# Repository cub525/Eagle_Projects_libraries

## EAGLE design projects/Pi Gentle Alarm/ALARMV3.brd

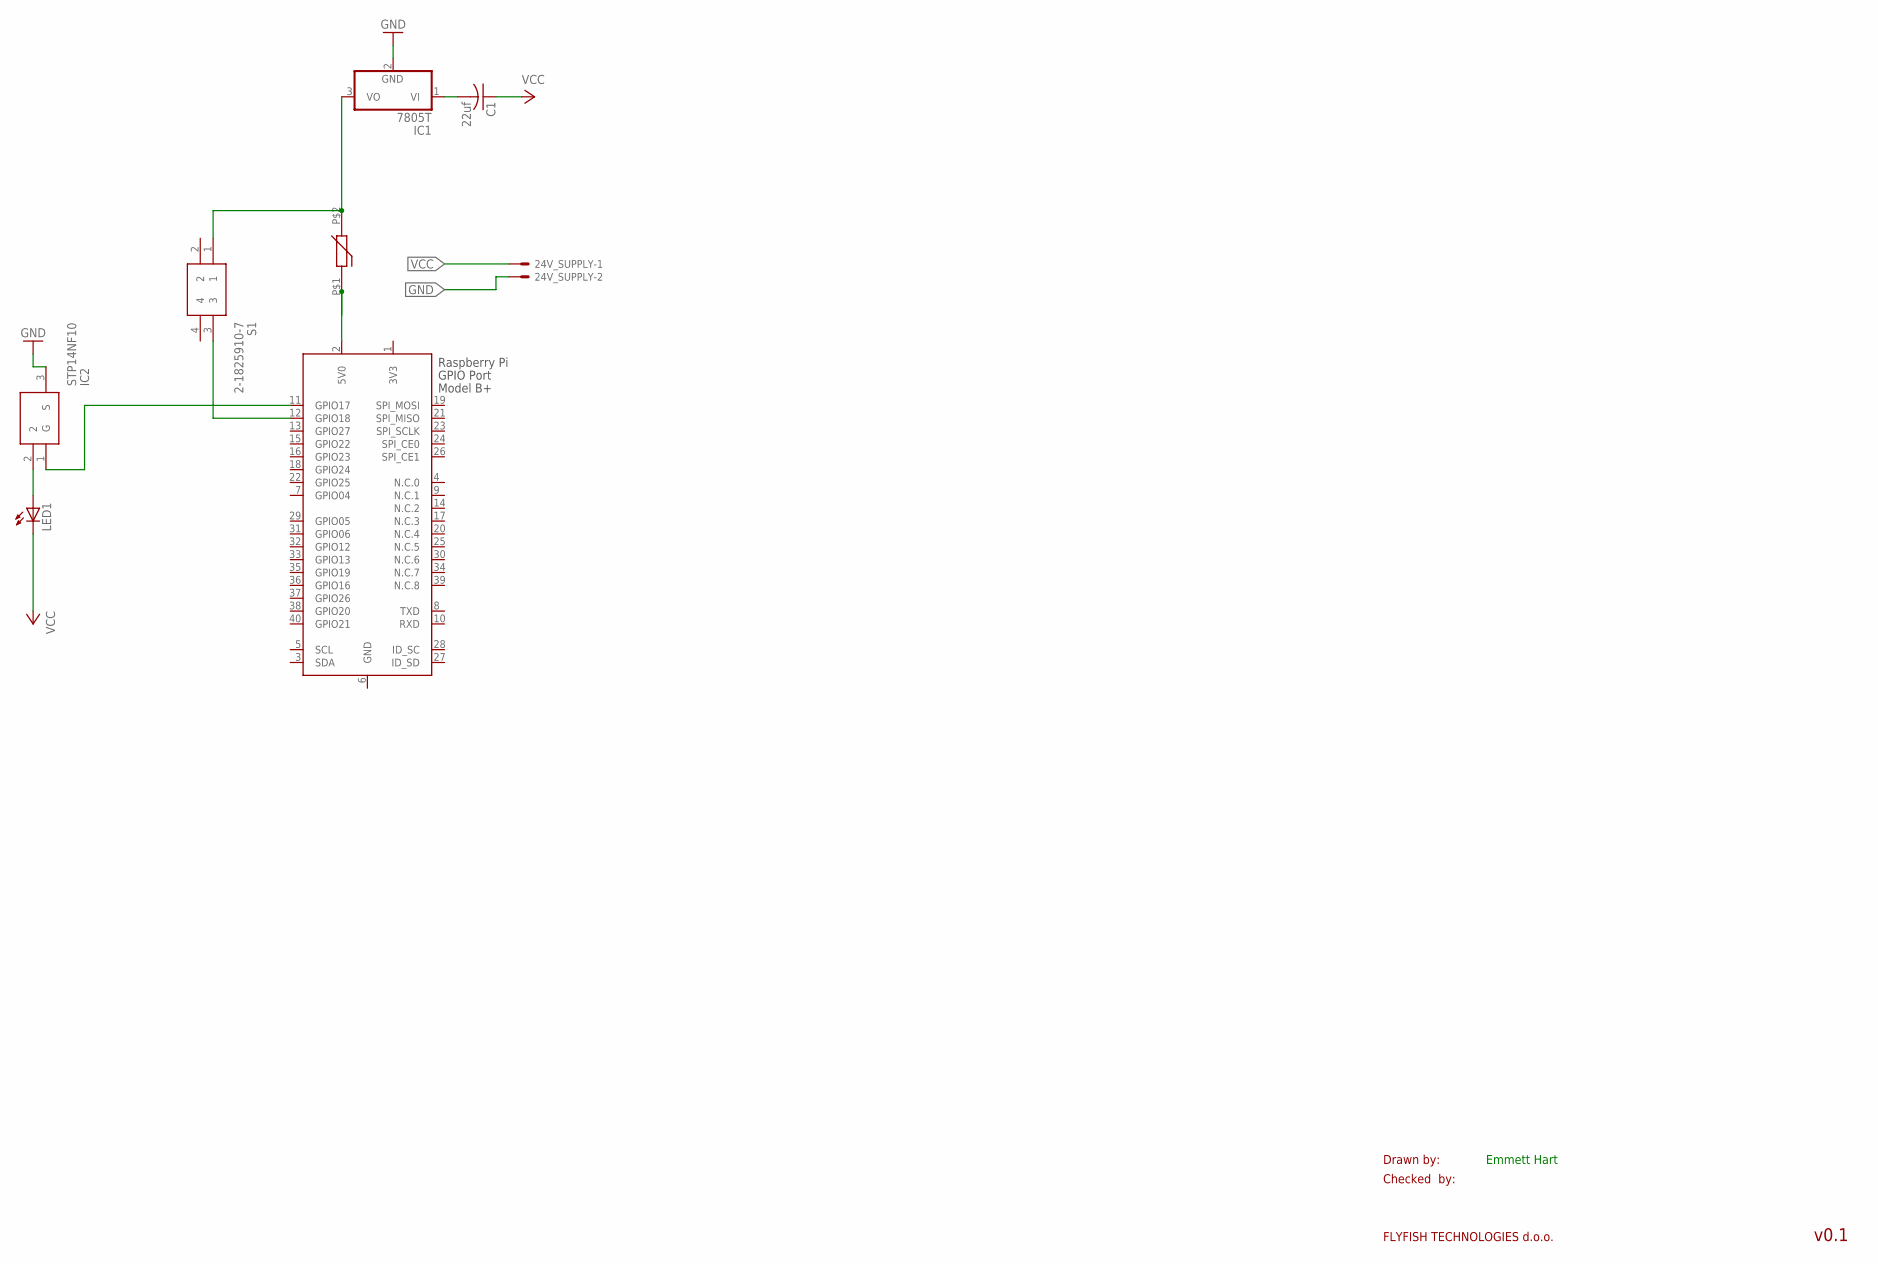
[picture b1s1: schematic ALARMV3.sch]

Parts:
24V_SUPPLY: 22-23-2021
C1: 22uf; C050-024X044
F1: MF-MSMF260-2
IC1: 7805T; TO220H; MPN NCP7805TG
IC2: STP14NF10; TO270P460X1020X2008-3P
LED1: LEDSFH482; SFH482
S1: 2-1825910-7; TE-6MM-TACT-SWITCH
X1: RASPI_BOARD_B+_E0; RASPI_BOARD_B+_EDGES_0DRILL

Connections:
3V3: X1.1 (3V3)
GND: 24V_SUPPLY.2, IC1.2 (GND), IC2.3 (S), X1.6 (GND)
GPIO17: IC2.1 (G), X1.11 (GPIO17)
unnamed: F1.P$1, X1.2 (5V0)
unnamed: S1.3, X1.12 (GPIO18)
unnamed: C1.2, IC1.1 (VI)
unnamed: F1.P$2, IC1.3 (VO), S1.1
unnamed: IC2.2, LED1.A
VCC: 24V_SUPPLY.1, C1.1, LED1.K (C)

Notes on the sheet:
Drawn by:
Checked by:
FLYFISH TECHNOLOGIES d.o.o.
v0.1
Emmett Hart

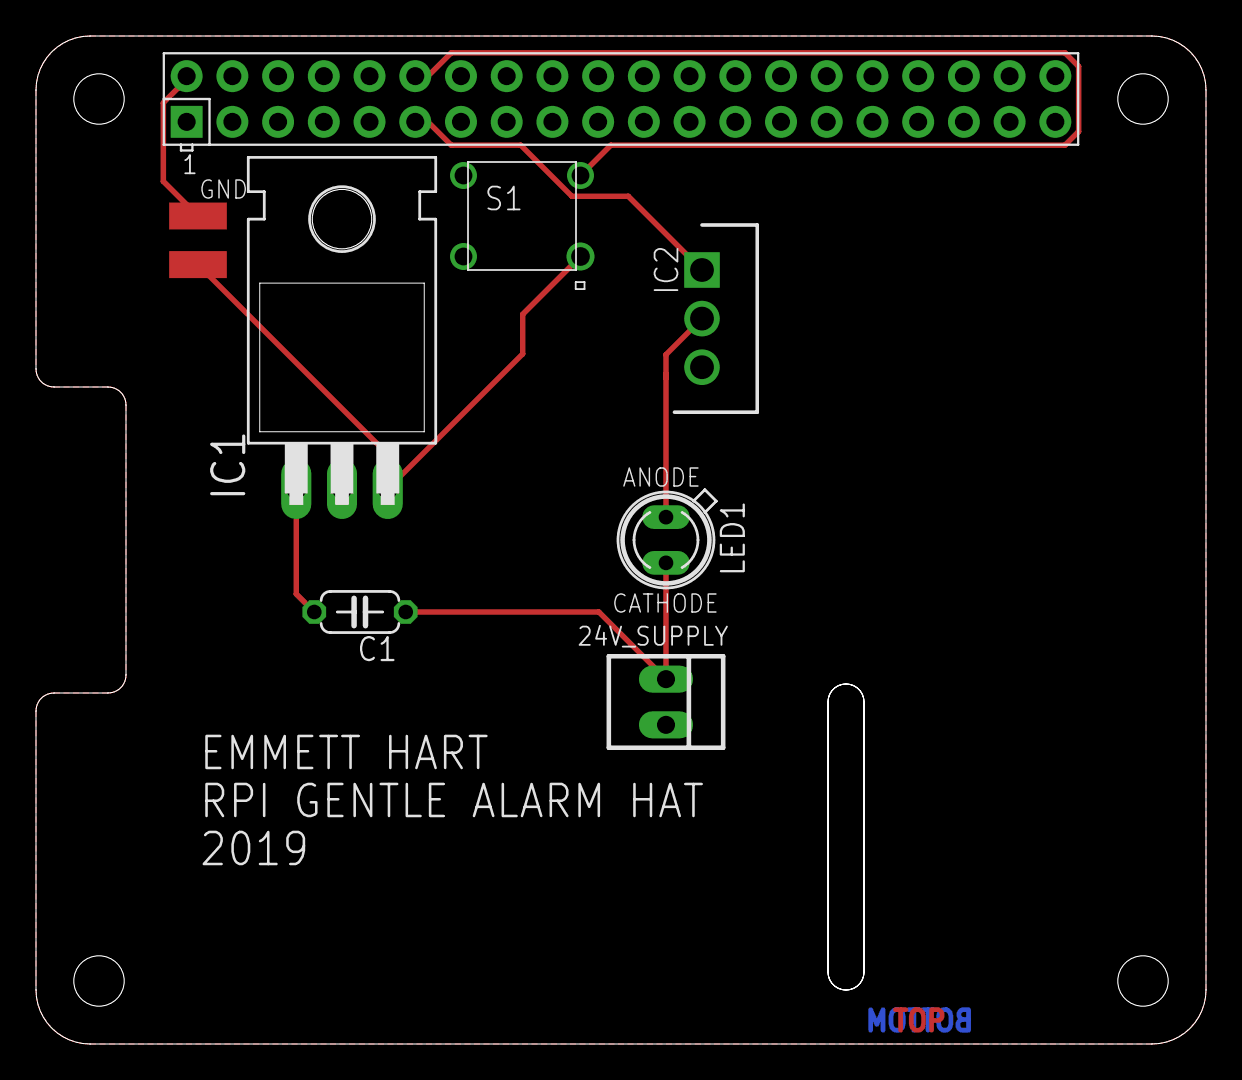
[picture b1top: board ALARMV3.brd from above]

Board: 2 copper layers, 65.0 x 56.0 mm, 8 parts (0 on the bottom side), 8 nets.

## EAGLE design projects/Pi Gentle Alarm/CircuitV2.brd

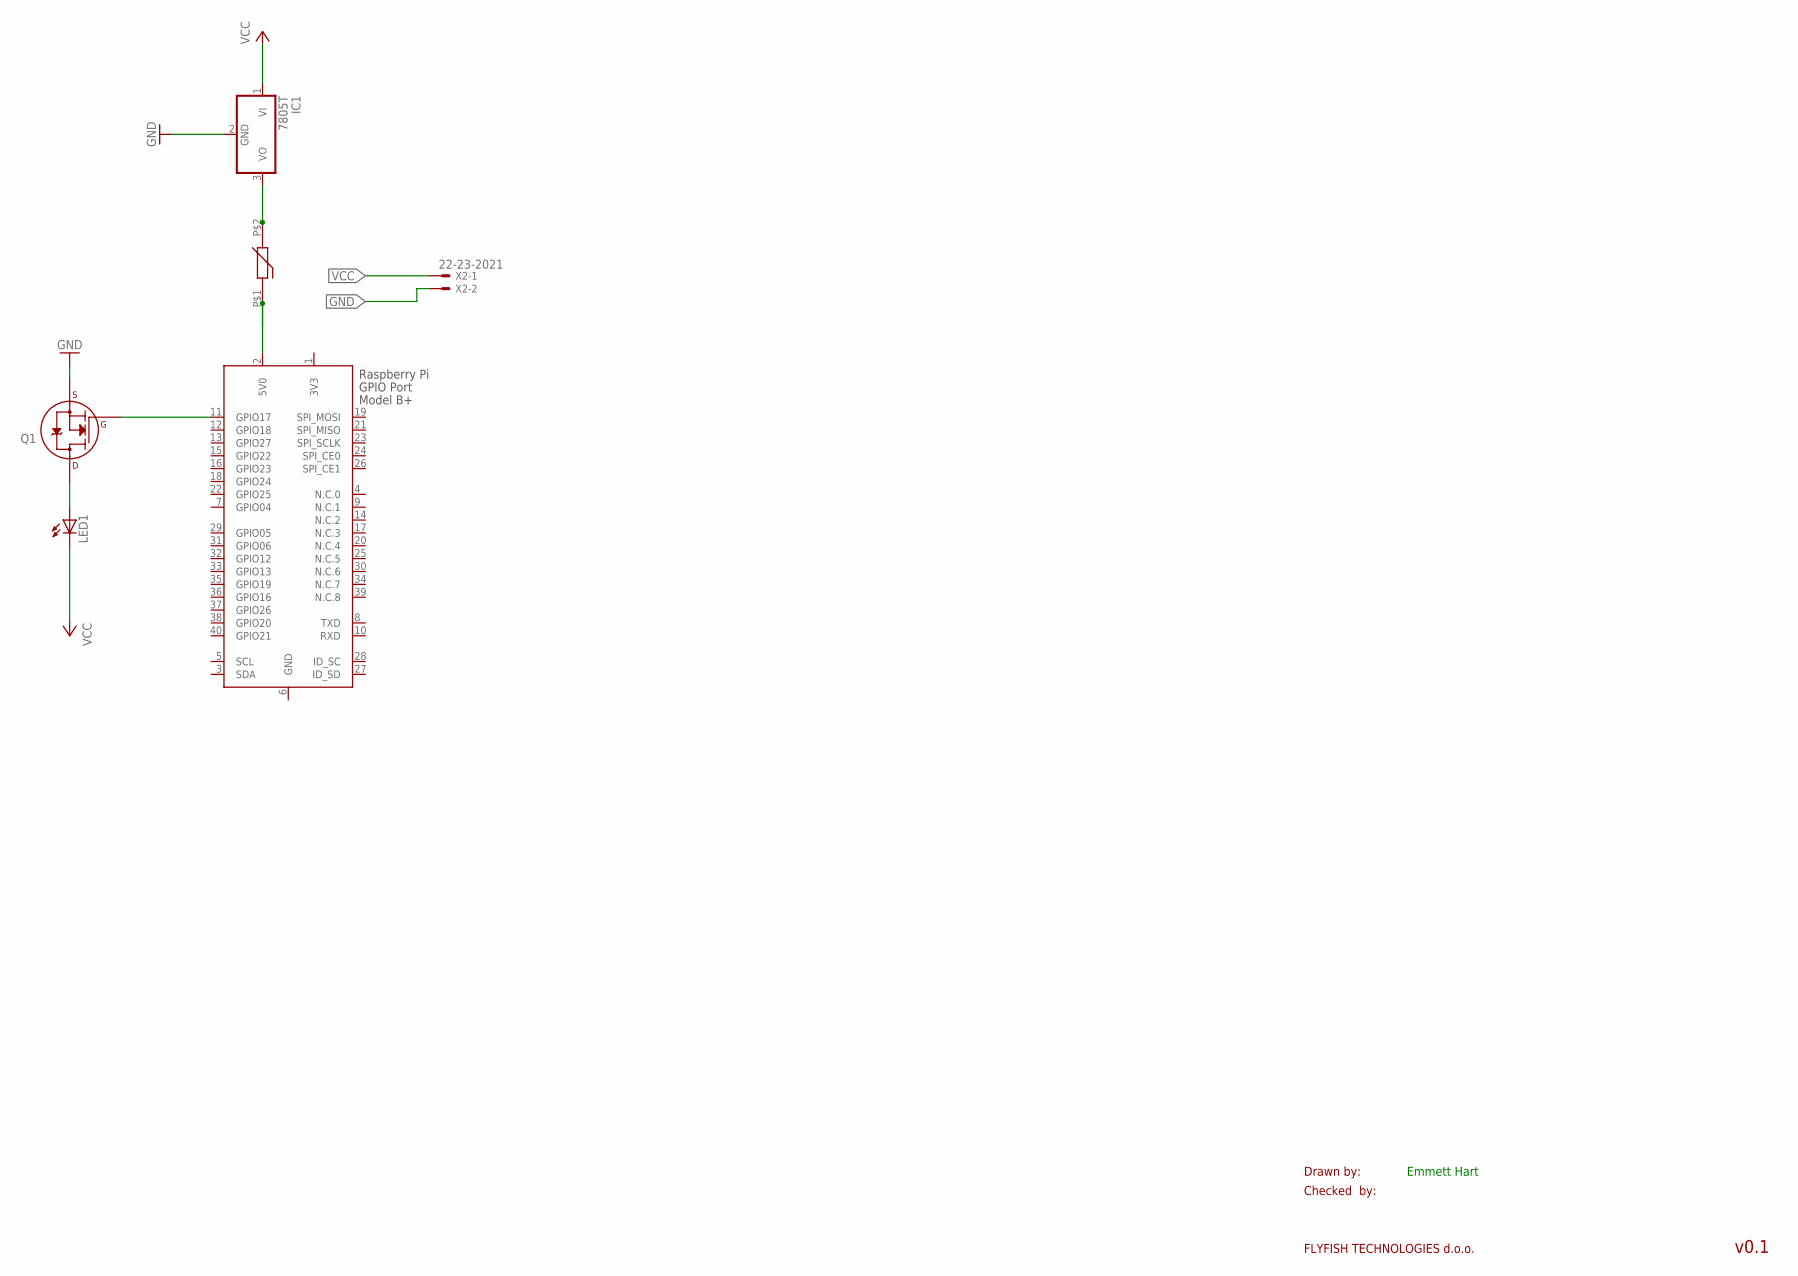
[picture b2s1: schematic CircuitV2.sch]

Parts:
F1: MF-MSMF260-2
IC1: 7805T; TO220H; MPN NCP7805TG
LED1: LEDSFH482; SFH482
Q1: 2N7000_TO92; TO-92; MPN 2N7000.
X1: RASPI_BOARD_B+_E0; RASPI_BOARD_B+_EDGES_0DRILL
X2: 22-23-2021

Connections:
3V3: X1.1 (3V3)
GND: IC1.2 (GND), Q1.1 (S), X1.6 (GND), X2.2
GPIO17: Q1.2 (G), X1.11 (GPIO17)
unnamed: F1.P$1, X1.2 (5V0)
unnamed: F1.P$2, IC1.3 (VO)
unnamed: LED1.A, Q1.3 (D)
VCC: IC1.1 (VI), LED1.K (C), X2.1

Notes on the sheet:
Drawn by:
Checked by:
FLYFISH TECHNOLOGIES d.o.o.
v0.1
Emmett Hart

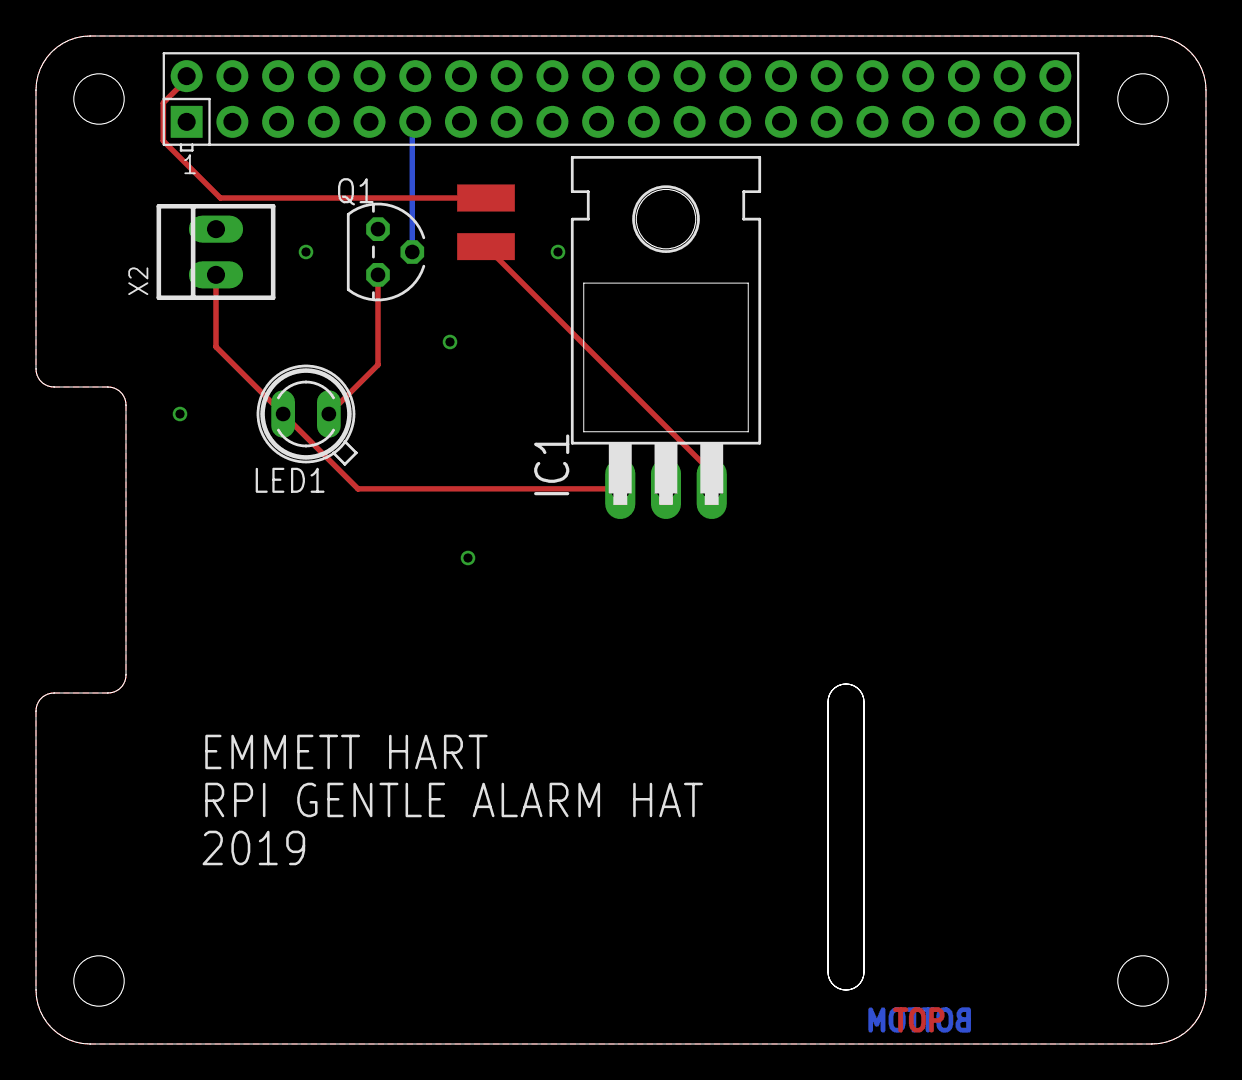
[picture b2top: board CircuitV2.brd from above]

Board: 2 copper layers, 65.0 x 56.0 mm, 6 parts (0 on the bottom side), 6 nets.

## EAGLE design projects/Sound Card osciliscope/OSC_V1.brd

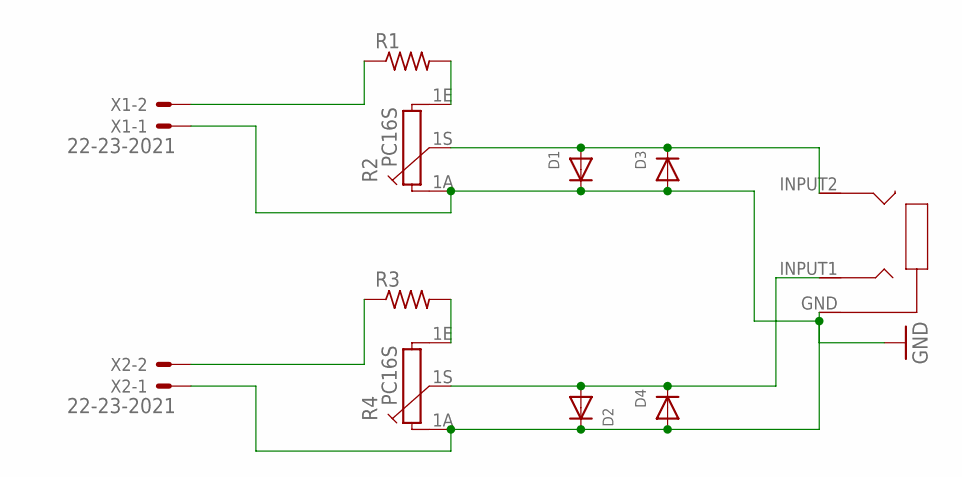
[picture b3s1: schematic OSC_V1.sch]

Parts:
D1, D2, D3, D4: DIODEDO-1N4148; DO-1N4148; MPN 1N4148 (DO-35)
R1, R3: R-US_0204/7; 0204/7
R2, R4: PC16S; MPN P160KN-0QC15B500K
U$1: AUDIO3PIN
X1, X2: 22-23-2021

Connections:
GND: D1.C, D2.C, D3.A, D4.A, R2.1A, R4.1A, U$1.GND, X1.1, X2.1
unnamed: R1.1, X1.2
unnamed: R1.2, R2.1E
unnamed: D1.A, D3.C, R2.1S, U$1.INPUT2
unnamed: R3.1, X2.2
unnamed: R3.2, R4.1E
unnamed: D2.A, D4.C, R4.1S, U$1.INPUT1

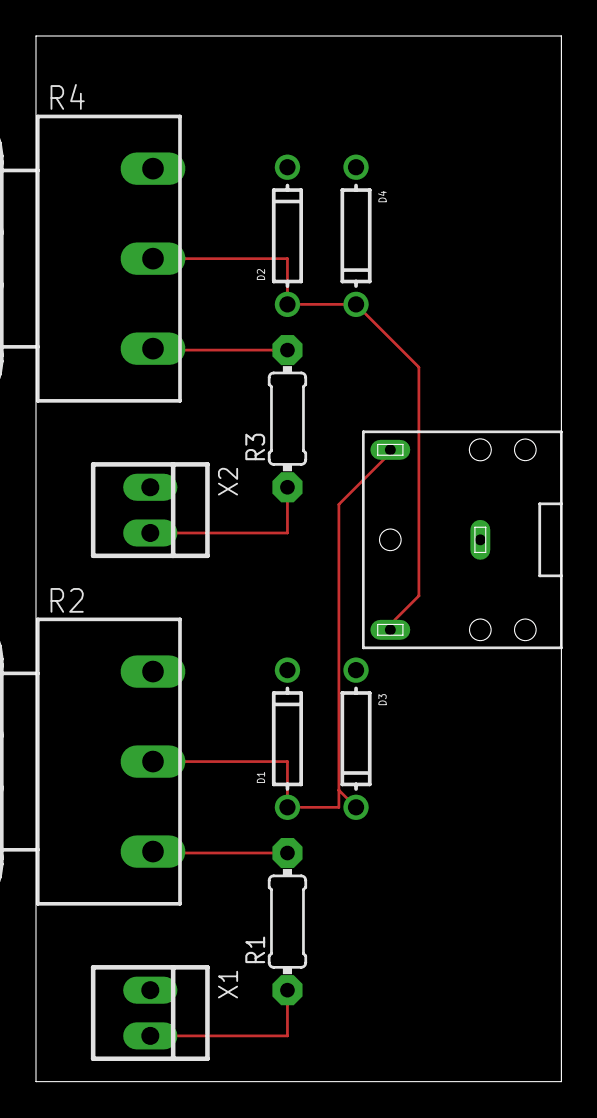
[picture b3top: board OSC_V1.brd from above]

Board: 2 copper layers, 29.2 x 58.1 mm, 11 parts (0 on the bottom side), 7 nets.

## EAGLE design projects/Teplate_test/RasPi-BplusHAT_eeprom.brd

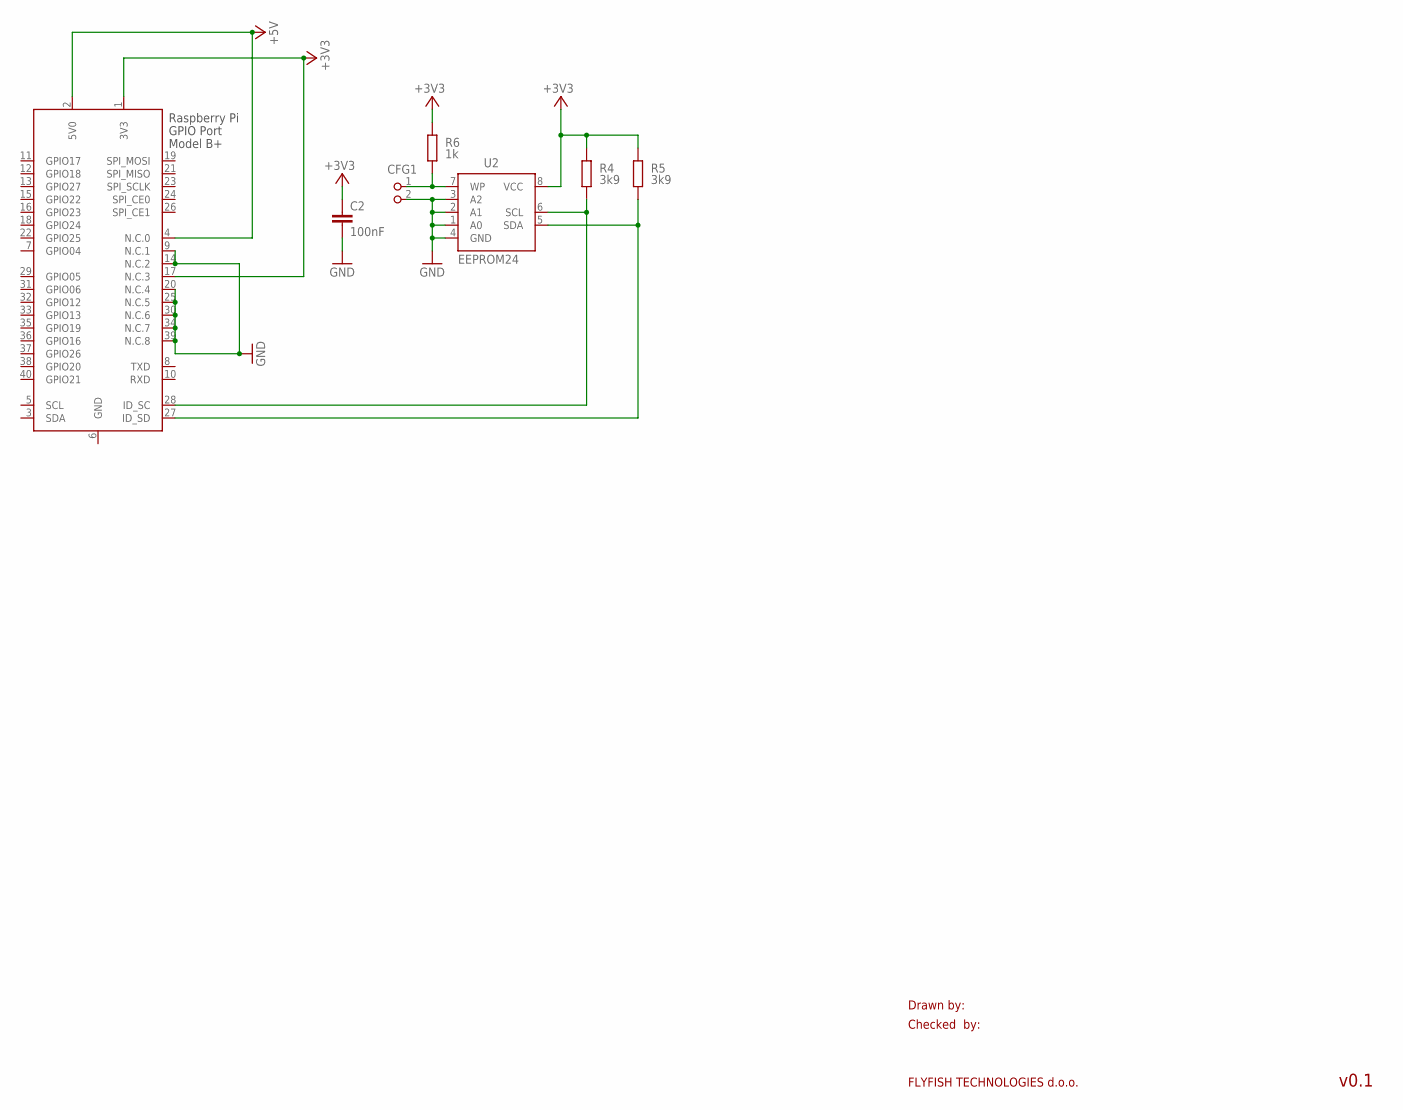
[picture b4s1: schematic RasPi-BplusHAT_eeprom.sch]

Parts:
C2: 100nF; C0805K
CFG1: PIN2_100; PIN_W_2
R4, R5: 3k9; M0805; TOLERANCE 5%
R6: 1k; M0805; TOLERANCE 5%
U2: EEPROM24; SOIC8
X1: RASPI_BOARD_B+_E0; RASPI_BOARD_B+_EDGES_0DRILL

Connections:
+3V3: C2.1, R4.2, R5.2, R6.2, U2.8 (VCC), X1.1 (3V3), X1.17 (N.C.3)
+5V: X1.2 (5V0), X1.4 (N.C.0)
GND: C2.2, CFG1.2, U2.1 (A0), U2.2 (A1), U2.3 (A2), U2.4 (GND), X1.6 (GND), X1.9 (N.C.1), X1.14 (N.C.2), X1.20 (N.C.4), X1.25 (N.C.5), X1.30 (N.C.6), X1.34 (N.C.7), X1.39 (N.C.8)
unnamed: R4.1, U2.6 (SCL), X1.28 (ID_SC)
unnamed: R5.1, U2.5 (SDA), X1.27 (ID_SD)
unnamed: CFG1.1, R6.1, U2.7 (WP)

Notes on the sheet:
Drawn by:
Checked by:
FLYFISH TECHNOLOGIES d.o.o.
v0.1

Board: 2 copper layers, 7 parts (0 on the bottom side), 6 nets, no tracks yet.

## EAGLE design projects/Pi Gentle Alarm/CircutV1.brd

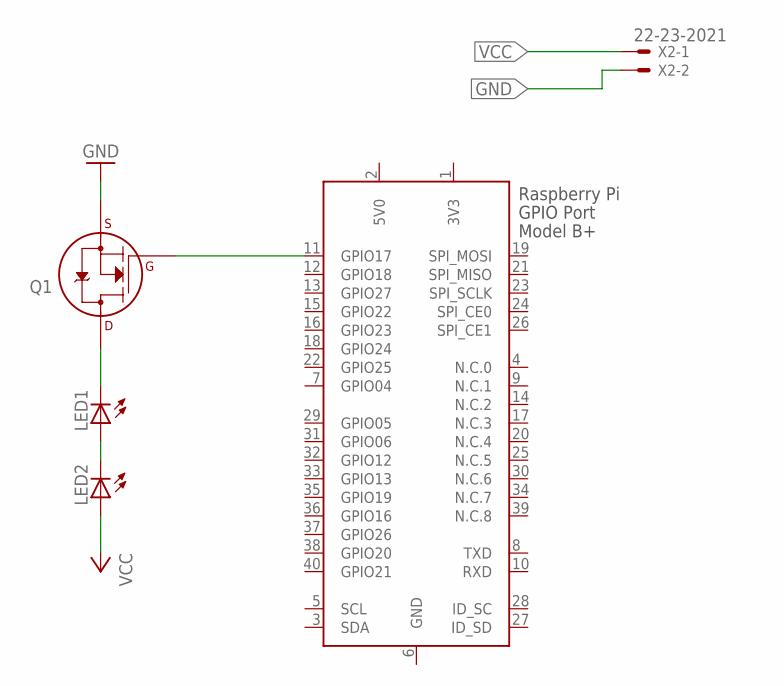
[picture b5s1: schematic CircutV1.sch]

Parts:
LED1, LED2: LED3MM
Q1: 2N7000_TO92; TO-92
X1: RASPI_BOARD_B+_E4; RASPI_BOARD_B+_EDGES_4DRILL
X2: 22-23-2021

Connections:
3V3: X1.1 (3V3)
5V0: X1.2 (5V0)
GND: Q1.1 (S), X1.6 (GND), X2.2
GPIO17: Q1.2 (G), X1.11 (GPIO17)
unnamed: LED1.A, LED2.K (C)
unnamed: LED1.K (C), Q1.3 (D)
VCC: LED2.A, X2.1

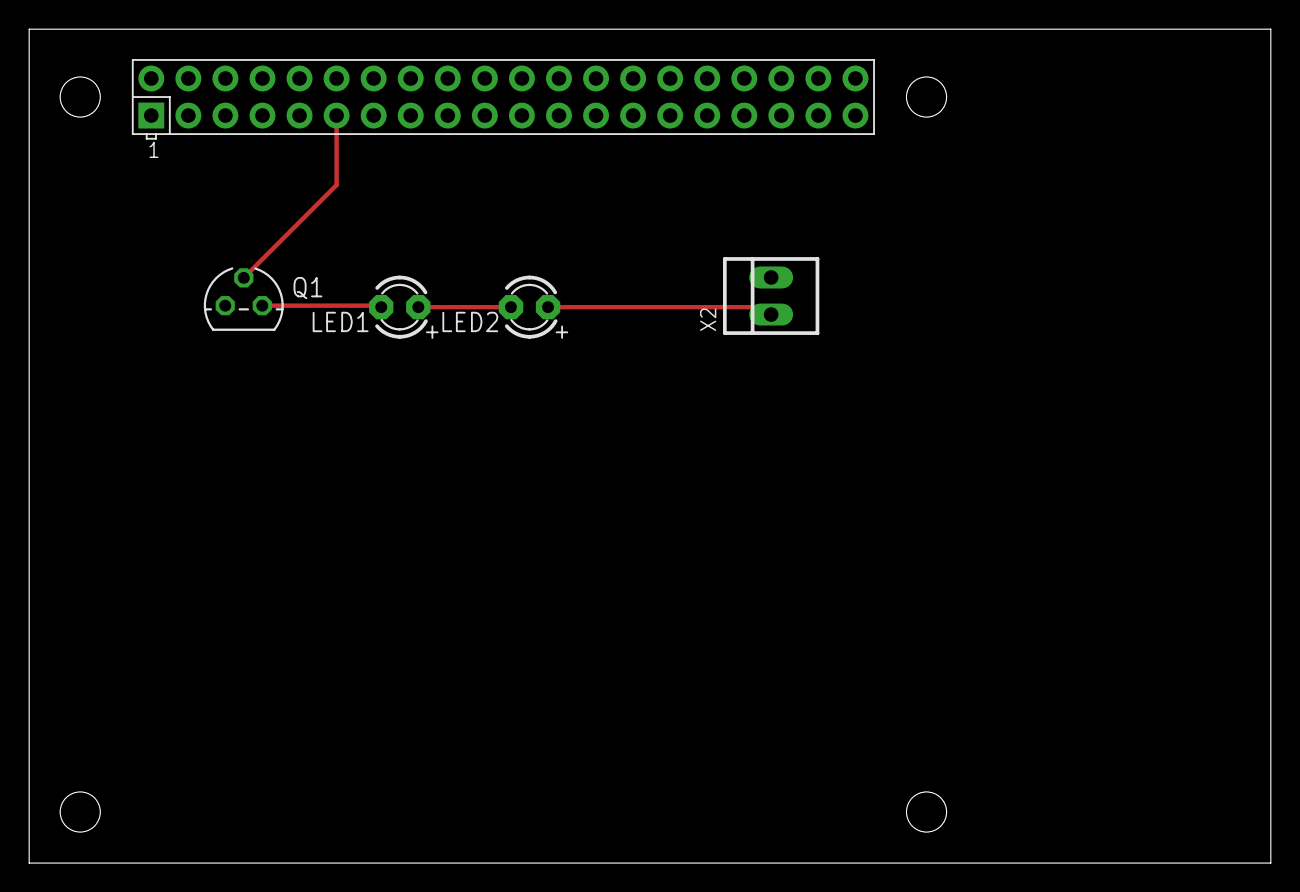
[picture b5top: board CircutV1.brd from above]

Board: 2 copper layers, 85.1 x 57.2 mm, 5 parts (0 on the bottom side), 5 nets.

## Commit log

2019-09-09 First test upload
2019-09-09 Added some templates for further use
2019-09-11 Changed directories for easy access
2019-09-11 Added a library to update the template
2019-09-11 Changed Template to be useful
2019-09-11 Added template to board
2019-09-11 Changed two LED to one Large ONe
2019-09-12 Added an EEPROM version of the template
2019-09-12 Added a fuse to board
2019-09-12 Started to add a 3pin audio jack
2019-09-13 Changed fuse to reflect chosen model
2019-09-13 Update Library and Sccope
    Added 3pin Jack to Library and finished up with the osciliscope
2019-09-13 Create LICENSE
2019-09-14 Finishing steps for the hat
    Added a fuse to protect the pi
2019-09-14 Changed order sheet
2019-09-14 Rewired and routed board
2019-09-14 Updated board
2019-09-14 Finalization of the Alarm
    Only steps are to post process and send
2019-09-14 Updated silkscreen
2019-09-14 Renamed files for convienence
2019-09-14 Deleted unnecessary files
2019-09-15 Processed with CAM to prepare for order
2019-09-15 Added a zipped folder for easy order.
2019-09-22 Added a button for turning off the alarm
2019-09-23 Satisfied dependancies
    Voltage regulator needed capacitors
    Changed shut-off button
2019-09-23 Removed extra components
2019-10-30 Added a part
